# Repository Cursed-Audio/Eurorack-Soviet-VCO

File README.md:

# Eurorack-Soviet-VCO
a CEM3340 based VCO in Eurorack Format.

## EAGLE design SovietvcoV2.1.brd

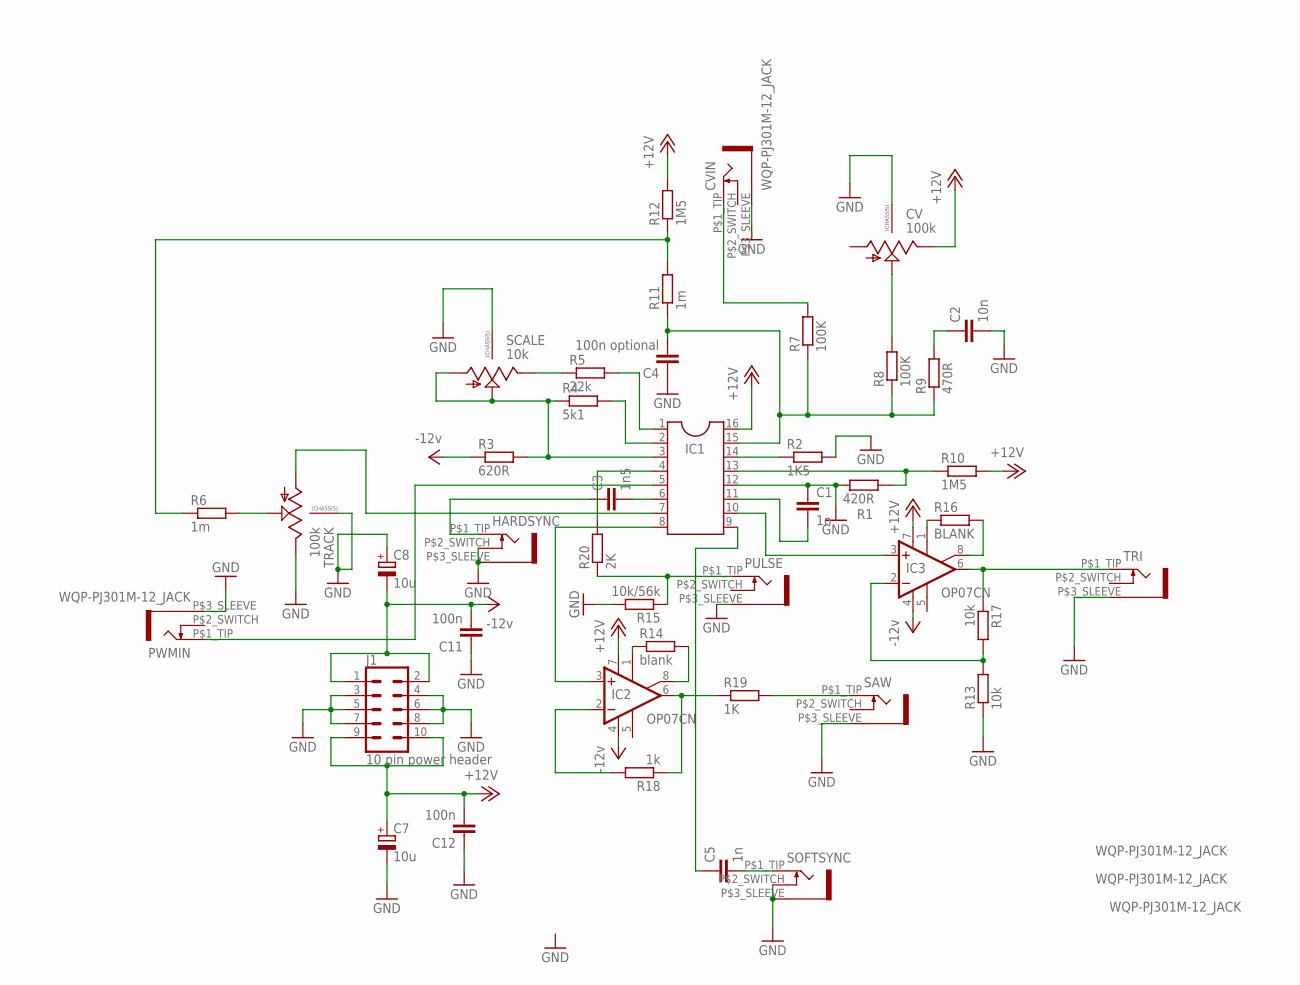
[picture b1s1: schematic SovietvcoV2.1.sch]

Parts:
C1, C5: 1n; C5B2.5
C2: 10n; C5B2.5
C3: 1n5; C5B2.5
C4: 100n optional; C5B2.5
C7, C8: 10u; E1,8-4
C11, C12: 100n; C5B2.5
CV: 100k; 9MM_SNAP-IN_POT
CVIN: WQP-PJ301M-12_JACK
HARDSYNC: WQP-PJ301M-12_JACK
IC1: CEM3340; SOCKET-16
IC2, IC3: OP07CN; DIL08
J1: 10 pin power header; 2X5-SHROUDED-NS
PULSE: WQP-PJ301M-12_JACK
PWMIN: WQP-PJ301M-12_JACK
R1: 420R; 0207/7
R2: 1K5; 0207/7
R3: 620R; 0207/7
R4: 5k1; 0207/7
R5: 22k; 0207/7
R6, R11: 1m; 0207/7
R7, R8: 100K; 0207/7
R9: 470R; 0207/7
R10, R12: 1M5; 0207/7
R13, R17: 10k; 0207/7
R14: blank; 0207/7
R15: 10k/56k; 0207/7
R16: BLANK; 0207/7
R18: 1k; 0207/7
R19: 1K; 0207/7
R20: 2K; 0207/7
SAW: WQP-PJ301M-12_JACK
SCALE: 10k; 9MM_SNAP-IN_POT
SOFTSYNC: WQP-PJ301M-12_JACK
TRACK: 100k; 9MM_SNAP-IN_POT
TRI: WQP-PJ301M-12_JACK

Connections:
+12V: C7.+, C12.2, CV.3 (E), IC1.16, IC2.7 (V+), IC3.7 (V+), J1.9, J1.10, R10.2, R12.2
-5V: IC2.4 (V-), IC3.4 (V-)
-12V: C8.-, C11.2, J1.1, J1.2, R3.1
GND: C1.1, C2.2, C4.1, C7.-, C8.+, C11.1, C12.1, CV.CHASSIS1, CV.CHASSIS2, CVIN.P$3_SLEEVE (1), IC1.12, J1.3, J1.4, J1.5, J1.6, J1.7, J1.8, PULSE.P$3_SLEEVE (1), PWMIN.P$3_SLEEVE (1), R1.1, R2.2, R13.1, R15.2, SAW.P$3_SLEEVE (1), SCALE.CHASSIS1, SCALE.CHASSIS2, TRACK.3 (E), TRACK.CHASSIS1, TRACK.CHASSIS2, TRI.P$3_SLEEVE (1)
unnamed: R5.1, SCALE.3 (E)
unnamed: IC1.3, R3.2, R4.1, SCALE.1 (A), SCALE.2 (S)
unnamed: C1.2, IC1.11
unnamed: C4.2, IC1.15, R7.1, R8.1, R9.1, R11.1
unnamed: IC1.13, R1.2, R10.1
unnamed: IC1.14, R2.1
unnamed: IC1.8, IC2.3 (+IN)
unnamed: IC1.2, R4.2
unnamed: IC2.1 (ON1), R14.1
unnamed: IC1.7, TRACK.1 (A)
unnamed: IC1.1, R5.2
unnamed: IC3.6 (OUT), R17.1, TRI.P$1_TIP (2)
unnamed: R6.2, TRACK.2 (S)
unnamed: CVIN.P$1_TIP (2), R7.2
unnamed: IC3.2 (-IN), R13.2, R17.2
unnamed: R6.1, R11.2, R12.1
unnamed: PULSE.P$1_TIP (2), R15.1, R20.1
unnamed: C5.1, IC1.9
unnamed: IC2.6 (OUT), R18.1, R19.1
unnamed: C5.2, SOFTSYNC.P$1_TIP (2)
unnamed: HARDSYNC.P$2_SWITCH (3), HARDSYNC.P$3_SLEEVE (1), SOFTSYNC.P$3_SLEEVE (1)
unnamed: IC2.8 (ON2), R14.2
unnamed: IC3.1 (ON1), R16.1
unnamed: C2.1, R9.2
unnamed: CV.2 (S), R8.2
unnamed: IC3.8 (ON2), R16.2
unnamed: C3.2, IC1.6
unnamed: R19.2, SAW.P$1_TIP (2)
unnamed: IC2.2 (-IN), R18.2
unnamed: C3.1, HARDSYNC.P$1_TIP (2)
unnamed: IC1.10, IC3.3 (+IN)
unnamed: IC1.4, R20.2
unnamed: IC1.5, PWMIN.P$1_TIP (2)

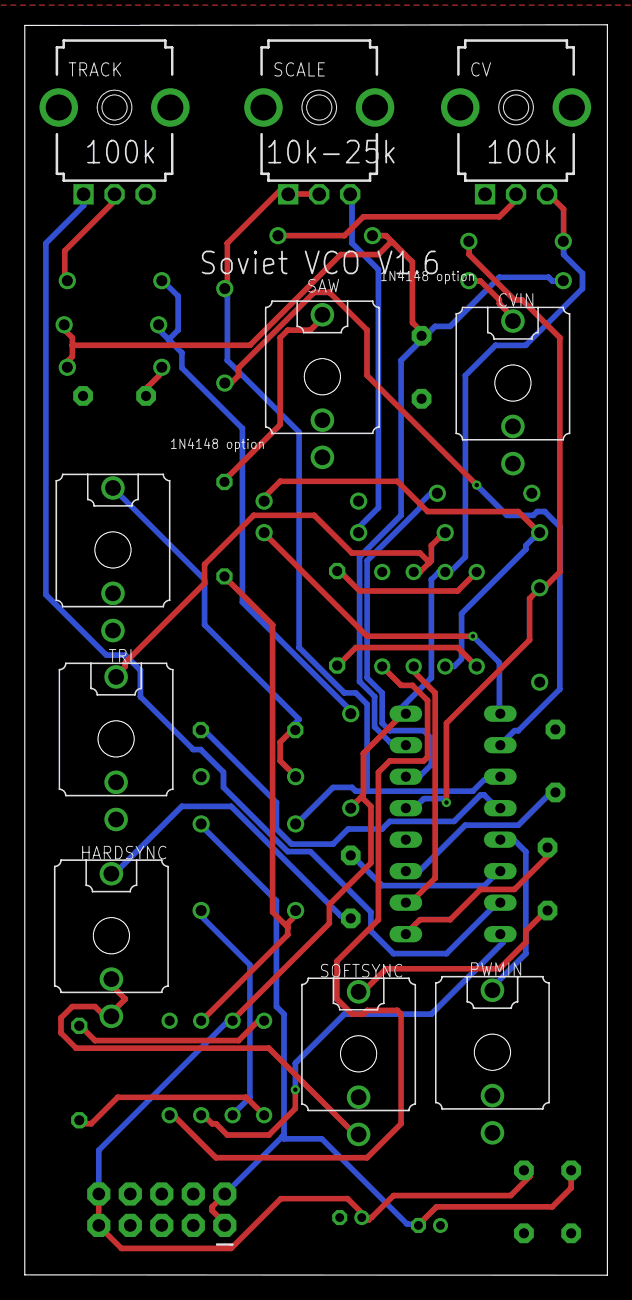
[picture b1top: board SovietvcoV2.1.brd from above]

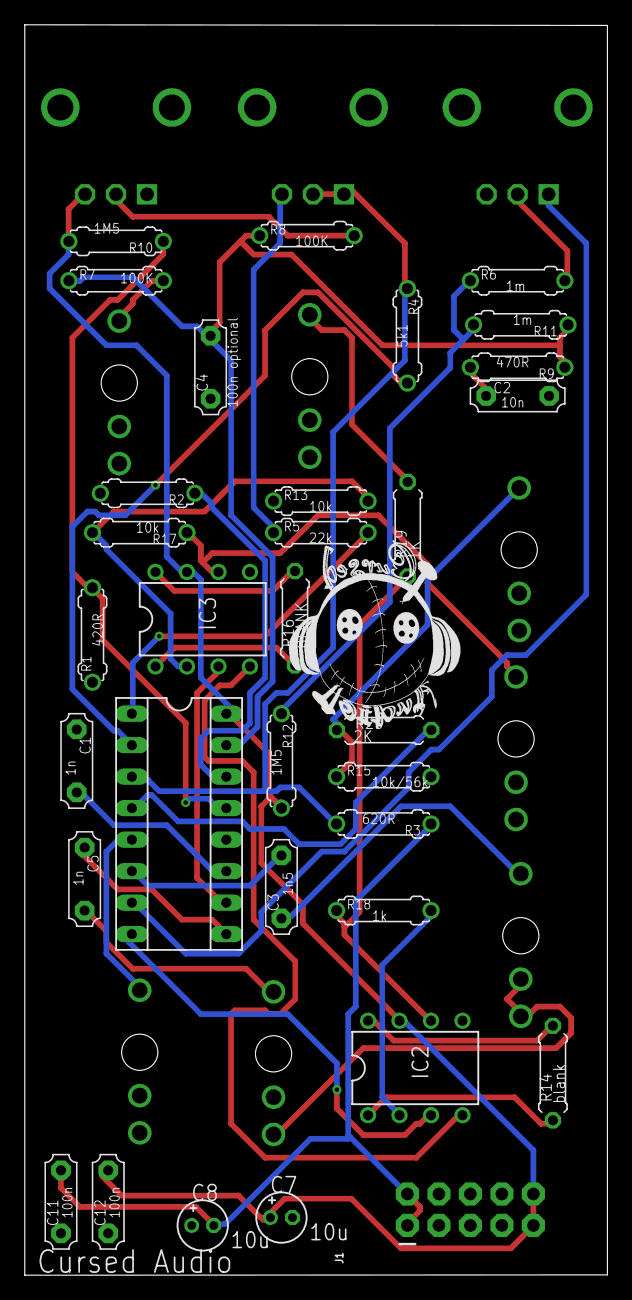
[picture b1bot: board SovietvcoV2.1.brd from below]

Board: 2 copper layers, 47.0 x 100.9 mm, 44 parts (33 on the bottom side), 37 nets.

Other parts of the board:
U$1: CA

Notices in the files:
parts and their libraries:
SparkFun-Connectors: Licensing: Creative Commons ShareAlike 4.0 International - https://creativecommons.org/licenses/by-sa/4.0
